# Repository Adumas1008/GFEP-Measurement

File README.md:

# GFEP-Measurement
A sample ground fault equipment protection measurement device

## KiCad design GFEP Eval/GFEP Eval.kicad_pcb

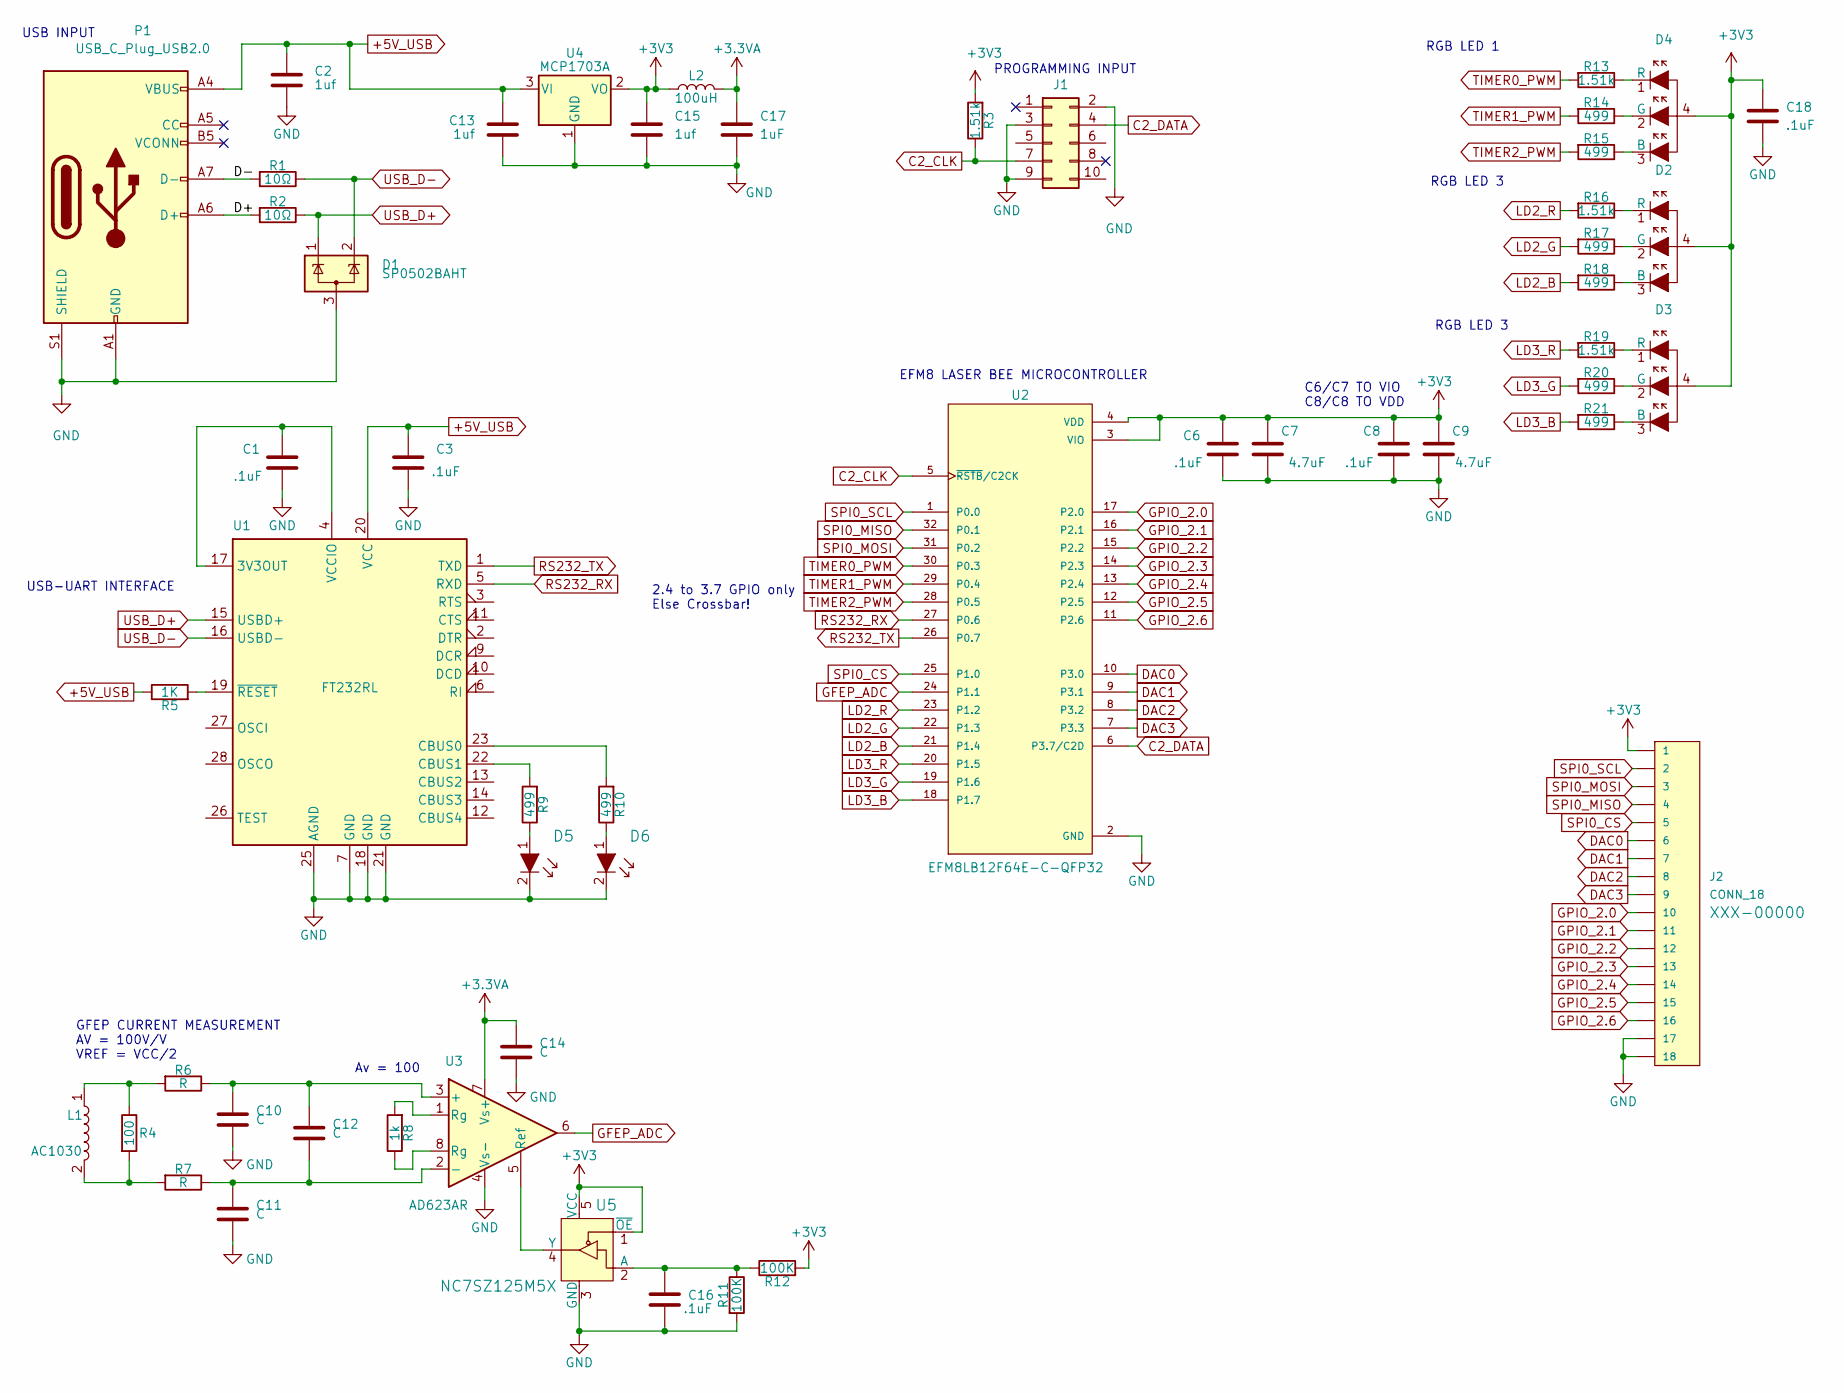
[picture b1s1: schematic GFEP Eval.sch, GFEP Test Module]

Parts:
C1, C3, C6, C8, C16, C18: .1uF; C_0603_1608Metric_Pad1.05x0.95mm_HandSolder
C2, C13, C15: 1uf; C_0805_2012Metric_Pad1.15x1.40mm_HandSolder
C7, C9: 4.7uF; C_0603_1608Metric_Pad1.05x0.95mm_HandSolder
C10, C11, C12, C14: C; C_0603_1608Metric_Pad1.05x0.95mm_HandSolder
C17: 1uF; C_0603_1608Metric_Pad1.05x0.95mm_HandSolder
D1: SP0502BAHT; SOT-23
D2, D3, D4: LTST-C19HE1WT; LED_Dual0603; MPN LTST-C19HE1WT; Digi-Key_PN 160-2162-1-ND
D5: LTST-C171KRKT; 0805; MPN LTST-C171KRKT; Digi-Key_PN 160-1427-1-ND
D6: LTST-C171KSKT; 0805; MPN LTST-C171KSKT; Digi-Key_PN 160-1428-1-ND
J1: Conn_02x05_Odd_Even; PinHeader_2x05_P2.54mm_Vertical
J2: CONN_18; PinHeader_2x09_P2.54mm_Vertical
L1: AC1030
L2: 100uH; L_0805_2012Metric_Pad1.15x1.40mm_HandSolder
P1: USB_C_Plug_USB2.0; USB_C_Receptacle_Amphenol_12401548E4-2A
R1, R2: 10Ω; R_0603_1608Metric_Pad0.98x0.95mm_HandSolder
R3, R13, R16, R19: 1.51k; R_0603_1608Metric_Pad0.98x0.95mm_HandSolder
R4: 100; R_1206_3216Metric_Pad1.30x1.75mm_HandSolder
R5: 1K; R_0603_1608Metric_Pad0.98x0.95mm_HandSolder
R6, R7: R; R_0603_1608Metric_Pad0.98x0.95mm_HandSolder
R8: 1k; R_0603_1608Metric_Pad0.98x0.95mm_HandSolder
R9, R10, R14, R15, R17, R18, R20, R21: 499; R_0603_1608Metric_Pad0.98x0.95mm_HandSolder
R11, R12: 100K; R_0603_1608Metric_Pad0.98x0.95mm_HandSolder
U1: FT232RL; SSOP-28_5.3x10.2mm_P0.65mm
U2: EFM8LB12F64E-C-QFP32; QFP80P900X900X120-32N; PARTREV C
U3: AD623AR; SO-8_3.9x4.9mm_P1.27mm
U4: MCP1703A; SOT-23
U5: NC7SZ125M5X; SOT-753; MPN NC7SZ125M5X; Digi-Key_PN NC7SZ125M5XCT-ND

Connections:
+3.3VA: C14.1, C17.1, L2.2, U3.7 (Vs+)
+3V3: C6.1, C7.1, C8.1, C9.1, C15.1, C18.1, D2.4, D3.4, D4.4, J2.1, L2.1, R3.2, R12.2, U2.3 (VIO), U2.4 (VDD), U4.2 (VO), U5.1 (~OE), U5.5 (VCC)
+5V_USB: C2.1, C3.1, C13.1, P1.A4 (VBUS), P1.A9 (VBUS), P1.B4 (VBUS), P1.B9 (VBUS), R5.1, U1.20 (VCC), U4.3 (VI)
/D+: P1.A6 (D+), R2.2
/D-: P1.A7 (D-), R1.2
C2_CLK: J1.7, R3.1, U2.5 (~RSTB~/C2CK)
C2_DATA: J1.4, U2.6 (P3.7/C2D)
DAC0: J2.6, U2.10 (P3.0)
DAC1: J2.7, U2.9 (P3.1)
DAC2: J2.8, U2.8 (P3.2)
DAC3: J2.9, U2.7 (P3.3)
GFEP_ADC: U2.24 (P1.1), U3.6
GND: C1.2, C2.2, C3.2, C6.2, C7.2, C8.2, C9.2, C10.2, C11.2, C13.2, C14.2, C15.2, C16.2, C17.2, C18.2, D1.3 (A), D5.2, D6.2, J1.2, J1.3, J1.9, J2.17, J2.18, P1.A1 (GND), P1.A12 (GND), P1.B1 (GND), P1.B12 (GND), P1.S1 (SHIELD), R11.2, U1.7 (GND), U1.18 (GND), U1.21 (GND), U1.25 (AGND), U2.2 (GND), U3.4 (Vs-), U4.1 (GND), U5.3 (GND)
GPIO_2.0: J2.10, U2.17 (P2.0)
GPIO_2.1: J2.11, U2.16 (P2.1)
GPIO_2.2: J2.12, U2.15 (P2.2)
GPIO_2.3: J2.13, U2.14 (P2.3)
GPIO_2.4: J2.14, U2.13 (P2.4)
GPIO_2.5: J2.15, U2.12 (P2.5)
GPIO_2.6: J2.16, U2.11 (P2.6)
LD2_B: R18.2, U2.21 (P1.4)
LD2_G: R17.2, U2.22 (P1.3)
LD2_R: R16.2, U2.23 (P1.2)
LD3_B: R21.2, U2.18 (P1.7)
LD3_G: R20.2, U2.19 (P1.6)
LD3_R: R19.2, U2.20 (P1.5)
unnamed: C1.1, U1.4 (VCCIO), U1.17 (3V3OUT)
unnamed: C10.1, C12.1, R6.1, U3.3 (+)
unnamed: C11.1, C12.2, R7.1, U3.2 (-)
unnamed: C16.1, R11.1, R12.1, U5.2 (A)
unnamed: D2.1 (R), R16.1
unnamed: D2.2 (G), R17.1
unnamed: D2.3 (B), R18.1
unnamed: D3.1 (R), R19.1
unnamed: D3.2 (G), R20.1
unnamed: D3.3 (B), R21.1
unnamed: D4.1 (R), R13.1
unnamed: D4.2 (G), R14.1
unnamed: D4.3 (B), R15.1
unnamed: D5.1, R9.1
unnamed: D6.1, R10.1
unnamed: L1.1, R4.1, R6.2
unnamed: L1.2, R4.2, R7.2
unnamed: R5.2, U1.19 (~RESET~)
unnamed: R8.1, U3.8 (Rg)
unnamed: R8.2, U3.1 (Rg)
unnamed: R9.2, U1.22 (CBUS1)
unnamed: R10.2, U1.23 (CBUS0)
unnamed: U3.5 (Ref), U5.4 (Y)
RS232_RX: U1.5 (RXD), U2.27 (P0.6)
RS232_TX: U1.1 (TXD), U2.26 (P0.7)
SPI0_CS: J2.5, U2.25 (P1.0)
SPI0_MISO: J2.4, U2.32 (P0.1)
SPI0_MOSI: J2.3, U2.31 (P0.2)
SPI0_SCL: J2.2, U2.1 (P0.0)
TIMER0_PWM: R13.2, U2.30 (P0.3)
TIMER1_PWM: R14.2, U2.29 (P0.4)
TIMER2_PWM: R15.2, U2.28 (P0.5)
USB_D+: D1.1 (K), R2.1, U1.15 (USBD+)
USB_D-: D1.2 (K), R1.1, U1.16 (USBD-)

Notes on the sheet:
Av = 100
GFEP CURRENT MEASUREMENT AV = 100V/V VREF = VCC/2
USB-UART INTERFACE
USB INPUT
PROGRAMMING INPUT
RGB LED 1
RGB LED 3
RGB LED 3
C6/C7 TO VIO C8/C8 TO VDD
EFM8 LASER BEE MICROCONTROLLER
2.4 to 3.7 GPIO only Else Crossbar!

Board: 2 copper layers, 53 parts (0 on the bottom side), 60 nets, no tracks yet.

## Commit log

2020-12-02 Initial Import
    Import existing initial directory and files
